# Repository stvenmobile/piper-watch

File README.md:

# Piper-Watch

**Piper-Watch** is the eyes of [piper-assistant](https://github.com/stvenmobile/piper_assistant):
a desktop robot head that turns to look around, finds and follows faces, and recognises the
people it knows. The head has two round display **eyes**, an OLED **mouth** and the camera as its
**nose**, so it can show what Piper is doing (listening, thinking, speaking) and who it is paying
attention to.

All the thinking happens on an **NVIDIA Jetson Orin NX** (a Seeed **reComputer J4012**), and
Piper-Watch sits right on top of it. **Level 2** - a 160 × 160 mm box over the reComputer -
holds the power wiring, the pan motor and a 4.3" display on its front. On top of Level 2, a lazy
Susan carries the **head**, which turns left and right. There is deliberately **no tilt motor**:
the camera is fixed 18° up, which suits a person sitting at the desk.

> **Status:** being built. Level 2's drive (deck, lazy Susan, belt and motor) has been built and
> test-fitted, its perfboard is laid out and the body is printing; the head's parts are printed.
> The firmware for the current design isn't written yet.

---

## Goals and non-goals

**Goals**

- Smooth, quiet tracking of a person's face (pan), without buzzing while holding still.
- Simple and stable: one motor, no tilt joint, everything wired inside.
- Face detection and recognition running entirely locally on the Jetson.
- A friendly, clearly-a-device presence: the eyes and mouth show Piper's state and look toward
  the person it is attending to, so it reads as an assistant, not a camera that silently watches.
- Compact: the footprint of the reComputer it sits on.
- One power supply for everything: the Jetson's own 19 V brick.

**Non-goals (for now)**

- Running any AI on the ESP32s.
- Battery operation.

---

## System architecture

```text
            ┌──────────────────────────── HEAD (turns) ─────────────────────────────┐
            │  XIAO ESP32-S3 ── SPI ──► two GC9A01 round eyes + SH1122 OLED mouth   │
            │  C920 camera board (the nose), fixed 18° up                            │
            └──────────┬──────────────────────────┬─────────────────────────────────┘
                       │ USB                       │ USB        (down the turntable's hollow tube)
            ┌──────────┼──────────────────────────┼─────── LEVEL 2 (fixed) ──────────────────────┐
            │          │                          │                                               │
            │  JC4827W543R 4.3" display (front) ── its own ESP32-S3 ──► TMC2209 ──► NEMA17 ── belt ── turntable
            │          │  1 frame/s camera view,   ▲ A3144 Hall (homing)                          │
            │          │  status page on a tap     │                                               │
            │  19 V jack ─ split block ─┬─ fuse ─ switch ─ perfboard (TMC2209 + 5 V buck)          │
            │                           └─ Jetson DC in                                            │
            └──────────┼──────────────────────────┼─────────────┬────────────────────────────────┘
                       │ USB                       │ USB         │ 19 V
            ┌──────────▼──────────────────────────▼─────────────▼────────────────────────────────┐
            │  reComputer J4012 (Jetson Orin NX)                                                   │
            │  vision: capture → face detection → recognition → tracking → pan target + face state │
            │  piper-assistant: speech in/out, dialogue; head link service; dashboard web page     │
            └──────────────────────────────────────────────────────────────────────────────────────┘
                 SP-200 USB speakerphone on the Jetson, placed away from the head
```

The roles are:

- **Jetson:** perception and decisions. It decides *where to look* and *what face to show*.
- **Level 2's display ESP32-S3:** the real-time body. It decides *how to move there* smoothly
  and safely, keeps track of where the head is, and runs the 4.3" screen.
- **Head XIAO ESP32-S3:** animates the eyes and mouth from the state it's sent.

Everything talks to the Jetson over USB; no Wi-Fi or Bluetooth is used.

---

## Components

| Part | Role |
| --- | --- |
| Seeed **reComputer J4012** (Jetson Orin NX, JetPack), with its 19 V brick | vision, recognition, assistant, dashboard; its brick powers everything |
| **Guition JC4827W543R** 4.3" 480 × 272 display with its own **ESP32-S3** (N4R8, native USB) | Level 2's front screen, and the pan motor's controller |
| **NEMA17** stepper (42.3 × 33.4 mm), 20-tooth GT2 pulley, 6 mm GT2 belt | pan motor; 5 : 1 onto the printed 100-tooth ring pulley |
| **BTT TMC2209** driver (STEP/DIR mode, 1/16 microstepping) | quiet stepper drive |
| **A3144** Hall switch + a magnet on the ring pulley | homing |
| 5.5" (140 mm) aluminium lazy Susan bearing | pan bearing, carries all the weight above it |
| **Seeed XIAO ESP32-S3** | the head's controller |
| 2 × 1.28" round **GC9A01** TFT (240 × 240) | the eyes |
| 2.08" **SH1122** OLED (256 × 64) | the mouth |
| Logitech **C920** camera board (out of its housing) | the nose - vision |
| **SP-200** USB speakerphone: 4-mic array, hardware echo cancellation | microphone and speaker, on the Jetson |
| 19 V panel jack (5.5 × 2.1, IP68), 2-way barrier strip, 6 × 30 mm panel fuse holder (3 A slow-blow), snap-in rocker switch | power entry on Level 2's back |
| LM2596S buck (set to 5.0 V), 70 × 50 perfboard, screw terminals, 100 µF / 35 V, 2 × 10 kΩ | the perfboard |
| Printed parts (PETG): Level 2 body and drive deck, motor bracket, ring pulley, head face, shell, camera plate and floor | enclosure and drive |

---

## Power

Everything runs from the **Jetson's own 19 V brick**. The 19 V comes in through a panel jack on
Level 2's back and is split on a barrier strip on Level 2's floor:

```text
19 V brick ── jack ── split block ──┬──────────────────────────────────────► Jetson DC in (always on)
                                    └── fuse (3 A slow) ── switch ── perfboard J1 ──┬── TMC2209 VM (+100 µF) ── NEMA17
                                                                                    └── LM2596 buck ── 5 V ── Hall sensor
split block − = the common ground (jack −, Jetson −, perfboard −)

Logic power comes over USB from the Jetson: Level 2's display (~260 mA), the head XIAO and its
three displays, and the camera.
```

- **The switch and fuse cover only the head side** (motor and buck). The Jetson's feed never
  passes through them, so switching the head off never cuts the Jetson.
- **The motor runs straight from 19 V:** the TMC2209 chops it down to the coil current, so
  there's no converter in that path.
- **The buck only feeds the Hall sensor** (it needs 5 V). Nothing with a USB link is fed from it,
  so nothing can back-feed the Jetson's USB ports.

The details - every wire, the perfboard layout and its wiring list - are in
[hardware/wiring.md](hardware/wiring.md).

---

## Wiring and pins

The full wiring is in [hardware/wiring.md](hardware/wiring.md), with KiCad schematics and the
perfboard drawings in [hardware/kicad/](hardware/kicad/). In short:

| Signal | Level 2 display (ESP32-S3) | Goes to |
| --- | --- | --- |
| STEP | IO 15 (connector P3) | TMC2209 STEP, through perfboard J4 |
| DIR | IO 16 (P3) | TMC2209 DIR |
| EN | IO 6 (P3) | TMC2209 EN (LOW = on); a 10 kΩ pull-up keeps the motor off while the ESP32 boots |
| HALL | IO 7 (P3) | A3144 output, 10 kΩ pull-up to 3.3 V |
| 3.3 V / GND | P4 | TMC2209 logic side, pull-ups |
| Jetson link + flashing | native USB (USB-C) | the Jetson |

The head's XIAO drives the two eyes and the mouth on one SPI bus with a chip select each; its
pins are in wiring.md's head section.

---

## Motion control

- **Drive:** the NEMA17 turns a 20-tooth pulley; the belt turns the 100-tooth ring pulley under
  the turntable, 5 : 1. With 1/16 microstepping that's **16,000 steps per turn** of the head
  (0.0225° each) - far finer than tracking needs, and the reduction gives plenty of torque.
- **Quiet:** the TMC2209 runs in StealthChop (its default in STEP/DIR mode), so holding still
  is silent and slow moves are close to it.
- **Step pulses come from hardware** (the S3's RMT/MCPWM), not the CPU, so drawing the screen
  can't make the pan stutter.
- **Homing:** at start-up the head turns slowly until the Hall sensor sees the magnet on the
  ring pulley; that's the zero. After that the position is counted in steps. Each time the
  head passes home the count is checked, so a missed step is caught and corrected.
- The Jetson sends **targets** (pan angle plus a speed hint) at up to 30–50 Hz. The ESP32 clamps
  them to the soft limits (about ±150°, set by the cables) and smooths them with a velocity and
  acceleration limit, so tracking looks natural rather than snappy.
- The ESP32 reports the **actual position** about 50 times a second, timestamped, so the Jetson
  knows where the camera was pointing when each video frame was taken. This is what keeps
  tracking stable while the head is moving.
- **Watchdog:**
  - no message from the Jetson for **1 s** → hold position;
  - for **10 s** → ease back to the rest pose, then disable the driver (silent, no holding current);
  - a fault (homing fails, the count is off at home) → stop and report.
- **Turning the head by hand:** with the driver disabled it turns freely through the belt.
  With the driver enabled, forcing it just skips steps (no gears to strip); the next pass over
  home corrects the count.

---

## Jetson ↔ ESP32 protocol (draft)

- **Link:** each ESP32-S3's native USB serial (`/dev/ttyACM*` on the Jetson). Native USB ignores
  the baud setting and runs at full USB speed.
- **Messages:** newline-delimited **JSON**, one object per line, each with a `"t"` (type) field.
  Unknown types and fields are ignored, so either side can be updated first.
- The **head link service** in piper-assistant (`src/piper_head/link.py`) is the one program that
  talks to the ESP32s. It sends heartbeats, forwards messages from the assistant and the vision
  service, and re-sends the last face state whenever a device (re)connects.

| Direction | Message | Contents | Device |
| --- | --- | --- | --- |
| Jetson → ESP32 | `HEARTBEAT` | sequence | both |
| Jetson → ESP32 | `FACE` | state (idle, listening, thinking, speaking, sleeping, error, offline), mood, attention direction | head |
| Jetson → ESP32 | `LOOK` | pan°, max speed, mode (track / glance / rest) | Level 2 |
| Jetson → ESP32 | `CONFIG` | soft limits, smoothing, brightness, etc. | both |
| Jetson → ESP32 | `FRAME` | a camera frame for the 4.3" screen, about once a second, in small chunks | Level 2 |
| Jetson → ESP32 | `HEALTH` | Jetson temperatures, load, memory, uptime - for the status page | Level 2 |
| ESP32 → Jetson | `STATUS` | actual pan, homed, ESP32 time, flags | Level 2 |
| ESP32 → Jetson | `EVENT` | boot, watchdog, fault, homed | both |

Frames are sent in small chunks so a `LOOK` never waits behind one.

---

## The face

The head's front has two round **GC9A01 eyes** and a 2.08" **OLED mouth**; the camera looks out
of a small window in the arch above them. The XIAO animates them from the `FACE` state and mood:
the eyes blink, glance and look toward the person being tracked (`attention`), and the mouth
moves while Piper's speech plays. The eyes are mounted upside down (their pin tabs point up into
the arch), so their image is rotated 180° in software.

**Level 2's 4.3" display** shows a camera view about once a second - greyscale, or a line drawing
of what the camera sees - and, on a tap, a **status page**: the Jetson's temperatures, load,
memory and uptime, Piper's state, and the motor's (homed, position). The full camera view with
boxes and names is on the Jetson's **dashboard web page**.

---

## Vision pipeline (Jetson)

- **Capture:** C920 via V4L2, MJPEG at 720p30 (1080p if needed). Once mounted, **lock focus and
  exposure** with `v4l2-ctl`, because autofocus hunting looks bad while tracking.
- **Face detection:** SCRFD or a YOLOv8-face model under **TensorRT**.
- **Recognition:** **ArcFace** embeddings (InsightFace), matched against a local gallery.
  **Enrolment** is a short guided capture of several angles. Embeddings stay on the Jetson, and
  a "forget me" command deletes a person.
- **Tracking:** keep a track ID per face. Turn the face's **horizontal** position into a pan
  target using the camera's field of view and the head's position *at the time of that frame*
  (from `STATUS`), with a deadband so the head isn't constantly making tiny corrections.
  **Vertically** there is no motor: the camera's view at its fixed 18° covers faces from about
  3° below to 40° above it, which takes in a seated person at 30–60 cm.
- **Behaviour (piper-assistant):** who to look at (speaker, newcomer, recognised person), idle
  glances, a rest pose, and face states that match the conversation.

---

## Mechanics

Pan only - no tilt motor. Bottom to top:

- **reComputer J4012** on the desk (130 × 121 × 58 mm).
- **Skirt** (not designed yet): carries Level 2 over the reComputer with an air gap above it.
- **Level 2 body:** a 160 × 160 mm rounded box, about 9 cm tall, printed in one piece.
  - Front: the 4.3" display behind a window, screwed to four tapped posts.
  - Back: the 19 V jack, fuse holder and rocker switch, and a low cable exit for the Jetson's
    19 V and the USB cables.
  - Floor: the 19 V split block, the 5 V buck and the perfboard. Vents high on both sides.
  - Corners: solid columns with heat-set inserts for the drive deck's four screws.
- **Drive deck:** Level 2's lid. Everything that turns hangs from it, so the whole drive lifts
  out of the body as one unit after four screws:
  - the lazy Susan's outer ring is screwed to a plinth on top;
  - the printed 100-tooth **ring pulley** is fixed to the inner ring and hangs through the deck,
    with a 50 mm hollow tube down its middle for the cables;
  - the NEMA17 hangs from a **sliding bracket** in the back-right corner; two slots let it slide
    out to tension the belt, reachable from above with everything assembled. The Hall sensor
    sits on the bracket, next to the ring pulley's magnet.
- **Head:** a box 135 mm wide, 70 deep and 88 tall with a half-round **arch** on top (123 mm in
  all), straight on the turntable plate - no neck:
  - **face plate:** the two eyes and the mouth, each dropped into a pocket from behind;
  - **shell:** sides, back and the arch; the camera plate holds the bare C920 board inside the
    arch at its fixed 18°;
  - **floor:** screws to the turntable plate and carries the XIAO; the cables go down through
    a hole in it into the ring pulley's hollow tube.
- **Cables:** the XIAO's and the camera's USB cables run down the hollow tube into Level 2 and
  out of the back, with a service loop for the ±150° of pan. Avoid slip rings for USB 2.0.
- **Noise:** the drive is quiet, but if movement noise still reaches the speakerphone,
  piper-assistant can pause or flag speech recognition while the head moves.

All the CAD is parametric OpenSCAD in [hardware/cad/](hardware/cad/).

---

## Repository layout

```text
firmware/head/   earlier ESP32-S3 DevKitC bring-up; to be replaced by the head (XIAO: eyes and
                 mouth) and Level 2 (display: screen and pan motor) firmware
jetson/          Jetson-side Python (vision, tracking); the head link service lives in piper-assistant
hardware/cad/    OpenSCAD models of every printed part, export.sh -> out/*.3mf
hardware/kicad/  KiCad schematics, the perfboard layout and its wiring drawings
hardware/wiring.md   the wiring: power, perfboard, motor, Hall sensor, head
docs/            design notes, datasheets
tools/           bench and calibration helpers
```

Face images and embeddings are never committed (`jetson/data/` is git-ignored), because this
repository is public.

---

## Roadmap

1. **Level 2 build:** print the body, wire the perfboard, fit everything, set the buck and the
   driver's current.
2. **Level 2 firmware:** STEP/DIR from hardware pulses, homing, soft limits, the watchdog,
   `LOOK` / `STATUS` over USB.
3. **Level 2 screen:** the status page on a tap, then the 1 frame/s camera view.
4. **Head firmware:** the XIAO drives the eyes and mouth from `FACE`: states, moods, blinks,
   glances toward the tracked person.
5. **Vision:** detection and tracking on the Jetson, closing the loop through `LOOK`.
6. **Recognition:** enrolment, gallery, names on the dashboard and in the assistant.
7. **Dashboard:** the camera view with overlays on the Jetson's web page.

## Open questions

- The final pan range, which depends on the cable routing through the hollow tube.
- The skirt between the reComputer and Level 2: its height and the airflow over the Jetson.
- The head link service with two ESP32s: telling them apart (USB serial number, or a hello
  `EVENT` at boot) and routing each message to the right one.
- The frame format for the 4.3" screen: greyscale JPEG or a line drawing, and the chunk size.

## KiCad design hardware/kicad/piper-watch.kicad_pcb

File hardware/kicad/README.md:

# Piper-Watch wiring schematics (KiCad)

Open `piper-watch.kicad_pro` in KiCad 10 (or 9). Schematic only - everything is hand-wired, so
there's no PCB. `piper-watch.pdf` is a plot of all the sheets.

| Sheet | What's on it |
|---|---|
| Power | 19 V panel jack, split block (common ground), panel fuse, head switch, Jetson feed, 5 V buck |
| Level 2 drive | the perfboard (TMC2209, C1/C2, R1/R2, J1 J3 J4 J5 J6), the JC4827W543R display's ESP32-S3 (its P3/P4 connectors), A3144 Hall, NEMA17 |
| Head | XIAO ESP32-S3, two GC9A01 eyes, SH1122 mouth OLED |

- Connections are made with net labels on short wire stubs, so parts can be moved around freely.
  Nets that cross sheets (`+19V`, `+19V_FUSED`, `+19V_SW`, `+5V`, `GND`) are global labels;
  the rest are local to their sheet.
- The modules (TMC2209, LM2596, JC4827 display IO, XIAO, GC9A01, SH1122, A3144, barrier strip) are
  in the project library `piper-watch.kicad_sym`; everything else is from KiCad's standard libraries.
- `tools/gen_schematics.py` generated the first draft from `../wiring.md`. Once the schematics
  have been edited in KiCad, the KiCad files are the source of truth - don't re-run the generator
  over hand edits.

Checks: `kicad-cli sch erc piper-watch.kicad_sch` (0 violations on the draft), and
`kicad-cli sch export pdf piper-watch.kicad_sch` to refresh the PDF.

## Perfboard (Level 2)

`perfboard_wiring.png` is the 70 x 50 perfboard as built: top view, back of the case at the top,
parts on the 2.54 mm hole grid, every pad labelled. Wires are soldered on the underside but drawn
as seen from the top: copper = bare solid wire (thick = 19 V, GND, motor), red = insulated wire
where a run has to cross another.

It's drawn from `piper-watch.kicad_pcb`, which KiCad checks against the schematic (DRC: no
unconnected items, no schematic mismatches). Rebuild:

    "C:\Program Files\KiCad\10.0\bin\python.exe" tools/gen_perfboard.py   # placement + wire routing
    py -3 tools/plot_perfboard.py                                         # the picture (needs matplotlib)

Placement is the `PLACE` table in `gen_perfboard.py`; the wires are laid by a small grid router.

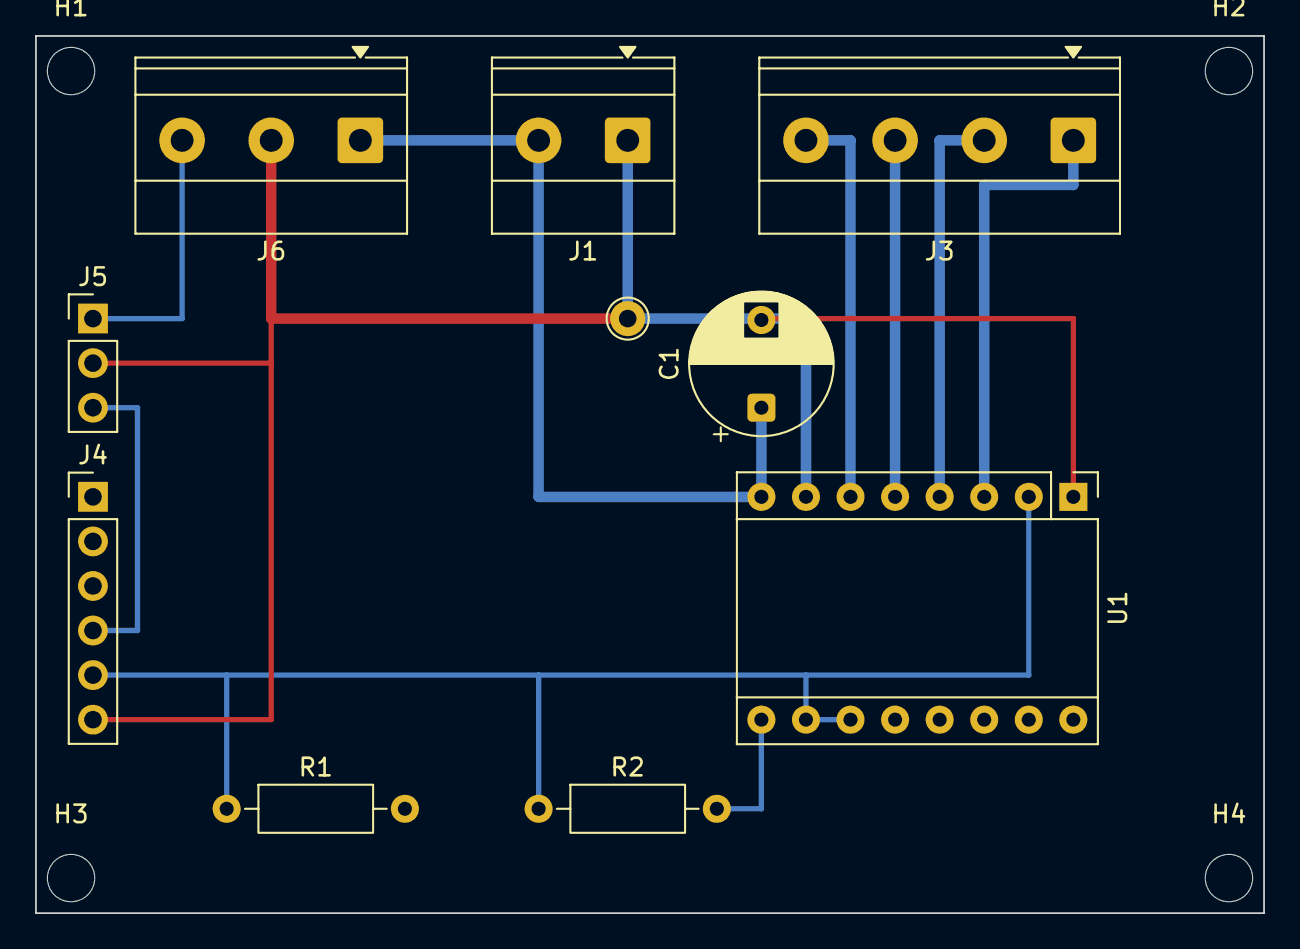
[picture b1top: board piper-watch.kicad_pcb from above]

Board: 4 copper layers, 70.0 x 50.0 mm, 14 parts (0 on the bottom side), 12 nets.

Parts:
C1: 100uF 35V (at U1 VS); CP_Radial_D8.0mm_P5.00mm
GP1: board ground point; TestPoint_THTPad_D2.0mm_Drill1.0mm
H1, H2, H3, H4: MountingHole_2.7mm_M2.5
J1: 19V in: + - left to right; TerminalBlock_Phoenix_MKDS-1,5-2-5.08_1x02_P5.08mm_Horizont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
J3: motor: A2 A1 B1 B2 (left to right on the board); TerminalBlock_Phoenix_MKDS-1,5-4-5.08_1x04_P5.08mm_Horizont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
J4: to display P3/P4: STEP DIR EN HALL 3V3 GND; PinHeader_1x06_P2.54mm_Vertical
J5: to Hall: 5V GND OUT; PinHeader_1x03_P2.54mm_Vertical
J6: to buck: 19V, GND, 5V; TerminalBlock_Phoenix_MKDS-1,5-3-5.08_1x03_P5.08mm_Horizont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
R1: 10k (Hall pull-up); R_Axial_DIN0207_L6.3mm_D2.5mm_P10.16mm_Horizontal
R2: 10k (EN pull-up); R_Axial_DIN0207_L6.3mm_D2.5mm_P10.16mm_Horizontal
U1: BTT TMC2209; Pololu_Breakout-16_15.2x20.3mm

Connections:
+5V: J5.1, J6.3
+19V_SW: C1.1, J1.2, J6.1, U1.8
/Level 2 drive/+3V3: J4.5, R1.1, R2.1, U1.2, U1.10, U1.11
/Level 2 drive/DIR: J4.2, U1.16
/Level 2 drive/EN: J4.3, R2.2, U1.9
/Level 2 drive/HALL: J4.4, J5.3, R1.2
/Level 2 drive/MOT_A1: J3.3, U1.5
/Level 2 drive/MOT_A2: J3.4, U1.6
/Level 2 drive/MOT_B1: J3.2, U1.4
/Level 2 drive/MOT_B2: J3.1, U1.3
/Level 2 drive/STEP: J4.1, U1.15
GND: C1.2, GP1.1, J1.1, J4.6, J5.2, J6.2, U1.1, U1.7
